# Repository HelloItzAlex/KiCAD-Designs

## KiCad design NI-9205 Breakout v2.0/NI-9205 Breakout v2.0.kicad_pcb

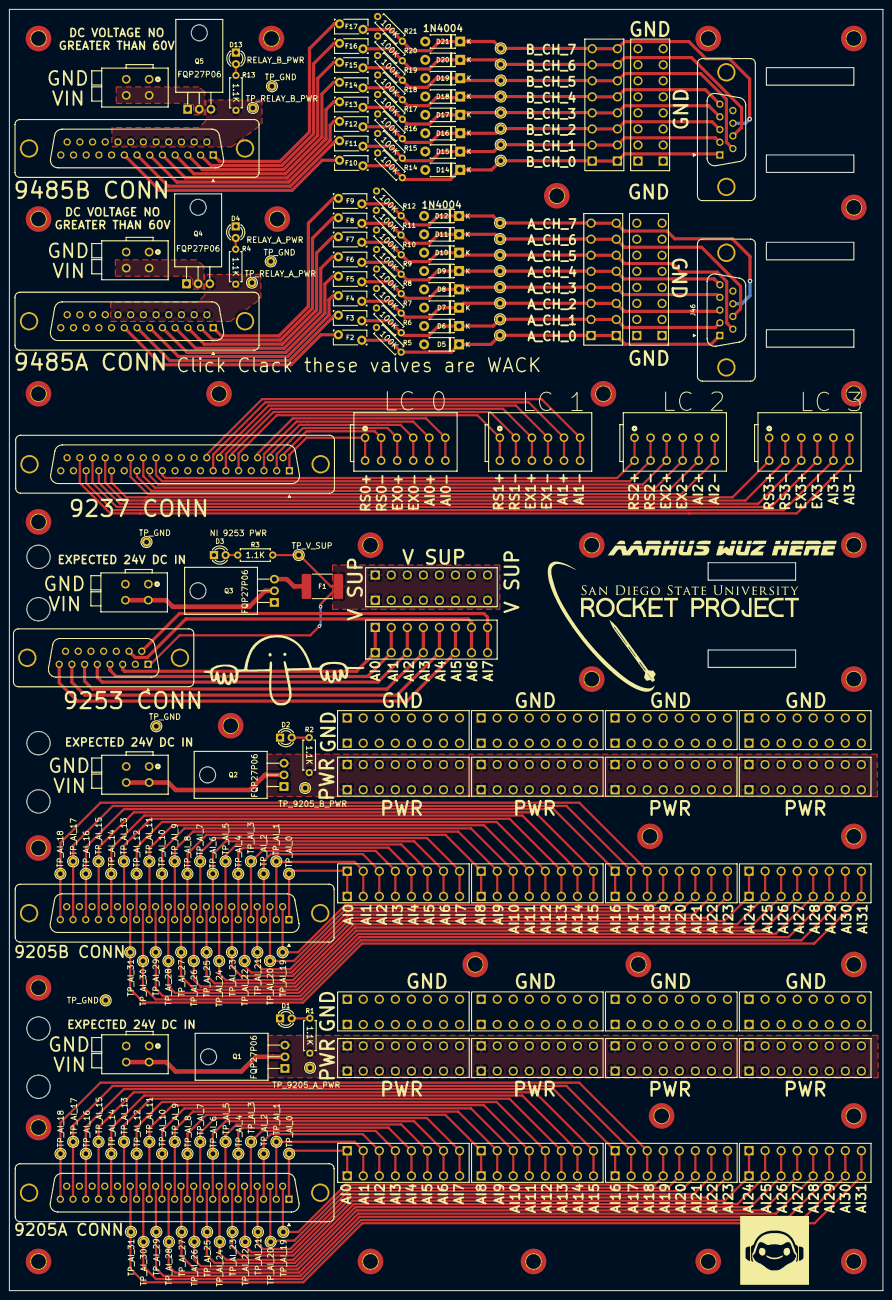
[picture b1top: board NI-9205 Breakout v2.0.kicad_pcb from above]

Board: 2 copper layers, 190.5 x 279.4 mm, 235 parts (0 on the bottom side), 145 nets.

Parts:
D1, D2, D3, D4, D13: LED; LED_D3.0mm
D5, D6, D7, D8, D9, D10, D11, D12, D14, D15, D16, D17, D18, D19, D20, D21: 1N4004; D_DO-41_SOD81_P7.62mm_Horizontal
F1: 0ZCF0100AF2A; Fuse_2920_7451Metric_Pad2.10x5.45mm_HandSolder
F2, F3, F4, F5, F6, F7, F8, F9, F10, F11, F12, F13, F14, F15, F16, F17: 0ZRP0065FF1E; Fuse_Bourns_MF-RG300
H1, H2, H3, H4, H5, H6, H7, H8, H9, H10, H11, H12, H13, H14, H15, H16, H17, H18, H19, H20, H21, H22, H23, H24, H25, H26, H27, H28, H29, H30, H31, H32, H33, H34: MountingHole_Pad; MountingHole_3.2mm_M3_DIN965_Pad_TopBottom
J1, J15: NI9205CONN; DSUB-37_Pins_Vertical_P2.77x2.84mm_MountingHoles
J2, J16, J32, J39, J43: PWRCONN; CONN2_2601-1102_WAG
J3, J6, J9, J13, J17, J20, J23, J27: 24VCONN; RHDR16W80P550X350_2X8_2870X850X1420P
J4, J7, J10, J14, J18, J21, J24, J28, J41, J45: GNDCONN; RHDR16W80P550X350_2X8_2870X850X1420P
J5, J8, J11, J12, J19, J22, J25, J26, J30, J40, J44: AICONN; RHDR16W80P550X350_2X8_2870X850X1420P
J29: NI9253CONN; DSUB-15_Pins_Vertical_P2.77x2.84mm_MountingHoles
J31: VSUPCONN; RHDR16W80P550X350_2X8_2870X850X1420P
J33: NI9237CONN; DSUB-37_Pins_Vertical_P2.77x2.84mm_MountingHoles
J34: LC0; CONN6_2601-3106_WAG
J35: LC1; CONN6_2601-3106_WAG
J36: LC2; CONN6_2601-3106_WAG
J37: LC3; CONN6_2601-3106_WAG
J38, J42: NI9485CONN; DSUB-25_Pins_Vertical_P2.77x2.84mm_MountingHoles
J46: NI_9485A_D-SUB; DSUB-9_Pins_Vertical_P2.77x2.84mm_MountingHoles
J47: NI_9485B_D-SUB; DSUB-9_Pins_Vertical_P2.77x2.84mm_MountingHoles
Q1, Q2, Q3, Q4, Q5: FQP27P06; TO-220-3_Horizontal_TabDown
R1, R2, R3, R4, R13: 1.1k; R_Axial_DIN0207_L6.3mm_D2.5mm_P7.62mm_Horizontal
R5, R6, R7, R8, R9, R10, R11, R12, R14, R15, R16, R17, R18, R19, R20, R21: 100K; R_Axial_DIN0207_L6.3mm_D2.5mm_P7.62mm_Horizontal
TP1, TP2, TP3, TP4, TP5, TP6, TP7, TP8, TP9, TP10, TP11, TP12, TP13, TP14, TP15, TP16, TP17, TP18, TP19, TP20, TP21, TP22, TP23, TP24, TP25, TP26, TP27, TP28, TP29, TP30, TP31, TP32, TP33, TP34, TP35, TP36, TP37, TP38, TP39, TP40, TP41, TP42, TP43, TP44, TP45, TP46, TP47, TP48, TP49, TP50, TP51, TP52, TP53, TP54, TP55, TP56, TP57, TP58, TP59, TP60, TP61, TP62, TP63, TP64, TP65, TP66, TP67, TP68, TP69, TP70, TP71, TP72, TP73, TP74, TP75, TP76, TP77, TP78, TP79, TP80, TP81, TP82, TP83, TP84, TP85, TP86, TP87, TP88, TP89, TP90: TestPoint; TestPoint_THTPad_D2.0mm_Drill1.0mm

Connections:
/V_IN_A: J39.3 (2_1), J39.4 (2_2), Q4.2 (D)
/V_IN_B: J43.3 (2_1), J43.4 (2_2), Q5.2 (D)
AI0: J29.3, J30.1, J30.2
AI1: J29.4, J30.3, J30.4
AI2: J29.5, J30.5, J30.6
AI3: J29.6, J30.7, J30.8
AI4: J29.7, J30.9, J30.10
AI5: J29.8, J30.11, J30.12
AI6: J29.10, J30.13, J30.14
AI7: J29.9, J30.15, J30.16
COM: D1.1 (K), D2.1 (K), D3.1 (K), D4.1 (K), D5.2 (A), D6.2 (A), D7.2 (A), D8.2 (A), D9.2 (A), D10.2 (A), D11.2 (A), D12.2 (A), D13.1 (K), D14.2 (A), D15.2 (A), D16.2 (A), D17.2 (A), D18.2 (A), D19.2 (A), D20.2 (A), D21.2 (A), J1.0 (PAD), J1.33, J2.1 (1_1), J2.2 (1_2), J4.1, J4.2, J4.3, J4.4, J4.5, J4.6, J4.7, J4.8, J4.9, J4.10, J4.11, J4.12, J4.13, J4.14, J4.15, J4.16, J7.1, J7.2, J7.3, J7.4, J7.5, J7.6, J7.7, J7.8, J7.9, J7.10, J7.11, J7.12, J7.13, J7.14, J7.15, J7.16, J10.1, J10.2, J10.3, J10.4, J10.5, J10.6, J10.7, J10.8, J10.9, J10.10, J10.11, J10.12, J10.13, J10.14, J10.15, J10.16, J14.1, J14.2, J14.3, J14.4, J14.5, J14.6, J14.7, J14.8, J14.9, J14.10, J14.11, J14.12, J14.13, J14.14, J14.15, J14.16, J15.0 (PAD), J15.33, J16.1 (1_1), J16.2 (1_2), J18.1, J18.2, J18.3, J18.4, J18.5, J18.6, J18.7, J18.8, J18.9, J18.10, J18.11, J18.12, J18.13, J18.14, J18.15, J18.16, J21.1, J21.2, J21.3, J21.4, J21.5, J21.6, J21.7, J21.8, J21.9, J21.10, J21.11, J21.12, J21.13, J21.14, J21.15, J21.16, J24.1, J24.2, J24.3, J24.4, J24.5, J24.6, J24.7, J24.8, J24.9, J24.10, J24.11, J24.12, J24.13, J24.14, J24.15, J24.16, J28.1, J28.2, J28.3, J28.4, J28.5, J28.6, J28.7, J28.8, J28.9, J28.10, J28.11, J28.12, J28.13, J28.14, J28.15, J28.16, J29.0 (PAD), J29.2, J32.1 (1_1), J32.2 (1_2), J38.0 (PAD), J39.1 (1_1), J39.2 (1_2), J41.1, J41.2, J41.3, J41.4, J41.5, J41.6, J41.7, J41.8, J41.9, J41.10, J41.11, J41.12, J41.13, J41.14, J41.15, J41.16, J42.0 (PAD), J43.1 (1_1), J43.2 (1_2), J45.1, J45.2, J45.3, J45.4, J45.5, J45.6, J45.7, J45.8, J45.9, J45.10, J45.11, J45.12, J45.13, J45.14, J45.15, J45.16, J46.0 (PAD), J46.9, J47.0 (PAD)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
EX0+: J33.2, J34.5 (3_1), J34.6 (3_2)
EX0-: J33.21, J34.7 (4_1), J34.8 (4_2)
EX1+: J33.6, J35.5 (3_1), J35.6 (3_2)
EX1-: J33.25, J35.7 (4_1), J35.8 (4_2)
EX2+: J33.12, J36.5 (3_1), J36.6 (3_2)
EX2-: J33.31, J36.7 (4_1), J36.8 (4_2)
EX3+: J33.16, J37.5 (3_1), J37.6 (3_2)
EX3-: J33.35, J37.7 (4_1), J37.8 (4_2)
NI9205A_AI0: J1.1, J5.1, J5.2, TP3.1
NI9205A_AI1: J1.2, J5.3, J5.4, TP4.1
NI9205A_AI2: J1.3, J5.5, J5.6, TP5.1
NI9205A_AI3: J1.4, J5.7, J5.8, TP6.1
NI9205A_AI4: J1.5, J5.9, J5.10, TP7.1
NI9205A_AI5: J1.6, J5.11, J5.12, TP8.1
NI9205A_AI6: J1.7, J5.13, J5.14, TP9.1
NI9205A_AI7: J1.8, J5.15, J5.16, TP10.1
NI9205A_AI8: J1.9, J8.1, J8.2, TP11.1
NI9205A_AI9: J1.10, J8.3, J8.4, TP12.1
NI9205A_AI10: J1.11, J8.5, J8.6, TP13.1
NI9205A_AI11: J1.12, J8.7, J8.8, TP14.1
NI9205A_AI12: J1.13, J8.9, J8.10, TP15.1
NI9205A_AI13: J1.14, J8.11, J8.12, TP16.1
NI9205A_AI14: J1.15, J8.13, J8.14, TP17.1
NI9205A_AI15: J1.16, J8.15, J8.16, TP18.1
NI9205A_AI16: J1.17, J11.1, J11.2, TP19.1
NI9205A_AI17: J1.18, J11.3, J11.4, TP20.1
NI9205A_AI18: J1.19, J11.5, J11.6, TP21.1
NI9205A_AI19: J1.20, J11.7, J11.8, TP22.1
NI9205A_AI20: J1.21, J11.9, J11.10, TP23.1
NI9205A_AI21: J1.22, J11.11, J11.12, TP24.1
NI9205A_AI22: J1.23, J11.13, J11.14, TP25.1
NI9205A_AI23: J1.24, J11.15, J11.16, TP26.1
NI9205A_AI24: J1.25, J12.1, J12.2, TP27.1
NI9205A_AI25: J1.26, J12.3, J12.4, TP28.1
NI9205A_AI26: J1.27, J12.5, J12.6, TP29.1
NI9205A_AI27: J1.28, J12.7, J12.8, TP30.1
NI9205A_AI28: J1.29, J12.9, J12.10, TP31.1
NI9205A_AI29: J1.30, J12.11, J12.12, TP32.1
NI9205A_AI30: J1.31, J12.13, J12.14, TP33.1
NI9205A_AI31: J1.32, J12.15, J12.16, TP34.1
NI9205A_PWR: J3.1, J3.2, J3.3, J3.4, J3.5, J3.6, J3.7, J3.8, J3.9, J3.10, J3.11, J3.12, J3.13, J3.14, J3.15, J3.16, J6.1, J6.2, J6.3, J6.4, J6.5, J6.6, J6.7, J6.8, J6.9, J6.10, J6.11, J6.12, J6.13, J6.14, J6.15, J6.16, J9.1, J9.2, J9.3, J9.4, J9.5, J9.6, J9.7, J9.8, J9.9, J9.10, J9.11, J9.12, J9.13, J9.14, J9.15, J9.16, J13.1, J13.2, J13.3, J13.4, J13.5, J13.6, J13.7, J13.8, J13.9, J13.10, J13.11, J13.12, J13.13, J13.14, J13.15, J13.16, Q1.3 (S), R1.1, TP1.1
NI9205B_AI0: J15.1, J19.1, J19.2, TP35.1
NI9205B_AI1: J15.2, J19.3, J19.4, TP36.1
NI9205B_AI2: J15.3, J19.5, J19.6, TP37.1
NI9205B_AI3: J15.4, J19.7, J19.8, TP38.1
NI9205B_AI4: J15.5, J19.9, J19.10, TP39.1
NI9205B_AI5: J15.6, J19.11, J19.12, TP40.1
NI9205B_AI6: J15.7, J19.13, J19.14, TP41.1
NI9205B_AI7: J15.8, J19.15, J19.16, TP42.1
NI9205B_AI8: J15.9, J22.1, J22.2, TP43.1
NI9205B_AI9: J15.10, J22.3, J22.4, TP44.1
NI9205B_AI10: J15.11, J22.5, J22.6, TP45.1
NI9205B_AI11: J15.12, J22.7, J22.8, TP46.1
NI9205B_AI12: J15.13, J22.9, J22.10, TP47.1
NI9205B_AI13: J15.14, J22.11, J22.12, TP48.1
NI9205B_AI14: J15.15, J22.13, J22.14, TP49.1
NI9205B_AI15: J15.16, J22.15, J22.16, TP50.1
NI9205B_AI16: J15.17, J25.1, J25.2, TP51.1
NI9205B_AI17: J15.18, J25.3, J25.4, TP52.1
NI9205B_AI18: J15.19, J25.5, J25.6, TP53.1
NI9205B_AI19: J15.20, J25.7, J25.8, TP54.1
NI9205B_AI20: J15.21, J25.9, J25.10, TP55.1
NI9205B_AI21: J15.22, J25.11, J25.12, TP56.1
NI9205B_AI22: J15.23, J25.13, J25.14, TP57.1
NI9205B_AI23: J15.24, J25.15, J25.16, TP58.1
NI9205B_AI24: J15.25, J26.1, J26.2, TP59.1
NI9205B_AI25: J15.26, J26.3, J26.4, TP60.1
NI9205B_AI26: J15.27, J26.5, J26.6, TP61.1
NI9205B_AI27: J15.28, J26.7, J26.8, TP62.1
NI9205B_AI28: J15.29, J26.9, J26.10, TP63.1
NI9205B_AI29: J15.30, J26.11, J26.12, TP64.1
NI9205B_AI30: J15.31, J26.13, J26.14, TP65.1
NI9205B_AI31: J15.32, J26.15, J26.16, TP66.1
NI9205B_PWR: J17.1, J17.2, J17.3, J17.4, J17.5, J17.6, J17.7, J17.8, J17.9, J17.10, J17.11, J17.12, J17.13, J17.14, J17.15, J17.16, J20.1, J20.2, J20.3, J20.4, J20.5, J20.6, J20.7, J20.8, J20.9, J20.10, J20.11, J20.12, J20.13, J20.14, J20.15, J20.16, J23.1, J23.2, J23.3, J23.4, J23.5, J23.6, J23.7, J23.8, J23.9, J23.10, J23.11, J23.12, J23.13, J23.14, J23.15, J23.16, J27.1, J27.2, J27.3, J27.4, J27.5, J27.6, J27.7, J27.8, J27.9, J27.10, J27.11, J27.12, J27.13, J27.14, J27.15, J27.16, Q2.3 (S), R2.1, TP89.1
NI9237_AI0+: J33.3, J34.9 (5_1), J34.10 (5_2)
NI9237_AI0-: J33.22, J34.11 (6_1), J34.12 (6_2)
NI9237_AI1+: J33.7, J35.9 (5_1), J35.10 (5_2)
NI9237_AI1-: J33.26, J35.11 (6_1), J35.12 (6_2)
NI9237_AI2+: J33.13, J36.9 (5_1), J36.10 (5_2)
NI9237_AI2-: J33.32, J36.11 (6_1), J36.12 (6_2)
NI9237_AI3+: J33.17, J37.9 (5_1), J37.10 (5_2)
NI9237_AI3-: J33.36, J37.11 (6_1), J37.12 (6_2)
NI9485A_24V+: J38.14, J38.15, J38.16, J38.17, J38.18, J38.19, J38.20, J38.21, Q4.3 (S), R4.1, TP69.1
NI9485A_CH0B: D5.1 (K), F2.2, J40.1, J40.2, J46.1, R5.1, TP71.1
NI9485A_CH1B: D6.1 (K), F3.2, J40.3, J40.4, J46.2, R6.1, TP72.1
NI9485A_CH2B: D7.1 (K), F4.2, J40.5, J40.6, J46.3, R7.1, TP73.1
NI9485A_CH3B: D8.1 (K), F5.2, J40.7, J40.8, J46.4, R8.1, TP74.1
NI9485A_CH4B: D9.1 (K), F6.2, J40.9, J40.10, J46.5, R9.1, TP75.1
NI9485A_CH5B: D10.1 (K), F7.2, J40.11, J40.12, J46.6, R10.1, TP76.1
NI9485A_CH6B: D11.1 (K), F8.2, J40.13, J40.14, J46.7, R11.1, TP77.1
NI9485A_CH7B: D12.1 (K), F9.2, J40.15, J40.16, J46.8, R12.1, TP78.1
NI9485B_24V+: J42.14, J42.15, J42.16, J42.17, J42.18, J42.19, J42.20, J42.21, Q5.3 (S), R13.1, TP79.1
NI9485B_CH0B: D14.1 (K), F10.2, J44.1, J44.2, J47.1, R14.1, TP81.1
NI9485B_CH1B: D15.1 (K), F11.2, J44.3, J44.4, J47.2, R15.1, TP82.1
NI9485B_CH2B: D16.1 (K), F12.2, J44.5, J44.6, J47.3, R16.1, TP83.1
NI9485B_CH3B: D17.1 (K), F13.2, J44.7, J44.8, J47.4, R17.1, TP84.1
NI9485B_CH4B: D18.1 (K), F14.2, J44.9, J44.10, J47.5, R18.1, TP85.1
NI9485B_CH5B: D19.1 (K), F15.2, J44.11, J44.12, J47.6, R19.1, TP86.1
NI9485B_CH6B: D20.1 (K), F16.2, J44.13, J44.14, J47.7, R20.1, TP87.1
NI9485B_CH7B: D21.1 (K), F17.2, J44.15, J44.16, J47.8, R21.1, TP88.1
unnamed: D1.2 (A), R1.2
unnamed: D2.2 (A), R2.2
unnamed: D3.2 (A), R3.2
unnamed: D4.2 (A), R4.2
unnamed: D13.2 (A), R13.2
unnamed: F2.1, J38.8
unnamed: F3.1, J38.7
unnamed: F4.1, J38.6
unnamed: F5.1, J38.5
unnamed: F6.1, J38.4
unnamed: F7.1, J38.3
unnamed: F8.1, J38.2
unnamed: F9.1, J38.1
unnamed: F10.1, J42.8
unnamed: F11.1, J42.7
unnamed: F12.1, J42.6
unnamed: F13.1, J42.5
unnamed: F14.1, J42.4
unnamed: F15.1, J42.3
unnamed: F16.1, J42.2
unnamed: F17.1, J42.1
unnamed: J2.3 (2_1), J2.4 (2_2), Q1.2 (D)
unnamed: J16.3 (2_1), J16.4 (2_2), Q2.2 (D)
unnamed: J32.3 (2_1), J32.4 (2_2), Q3.2 (D)
unnamed: F1.1, Q3.3 (S)
RS0+: J33.1, J34.1 (1_1), J34.2 (1_2)
RS0-: J33.20, J34.3 (2_1), J34.4 (2_2)
RS1+: J33.5, J35.1 (1_1), J35.2 (1_2)
RS1-: J33.24, J35.3 (2_1), J35.4 (2_2)
RS2+: J33.11, J36.1 (1_1), J36.2 (1_2)
RS2-: J33.30, J36.3 (2_1), J36.4 (2_2)
RS3+: J33.15, J37.1 (1_1), J37.2 (1_2)
RS3-: J33.34, J37.3 (2_1), J37.4 (2_2)
VSUP: F1.2, J29.1, J31.1, J31.2, J31.3, J31.4, J31.5, J31.6, J31.7, J31.8, J31.9, J31.10, J31.11, J31.12, J31.13, J31.14, J31.15, J31.16, R3.1, TP67.1

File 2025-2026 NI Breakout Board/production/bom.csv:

Designator,Footprint,Quantity,Value,LCSC Part #
"D1, D13, D2, D3, D4",LED_D3.0mm,5,LED,
"D10, D11, D12, D14, D15, D16, D17, D18, D19, D20, D21, D5, D6, D7, D8, D9",D_DO-41_SOD81_P7.62mm_Horizontal,16,1N4004,
F1,2920,1,0ZCF0100AF2A,
"F10, F11, F12, F13, F14, F15, F16, F17, F2, F3, F4, F5, F6, F7, F8, F9",Fuse_Bourns_MF-RG300,16,0ZRP0065FF1E,
"J1, J15",DSUB-37_Pins_Vertical_P2.77x2.84mm_MountingHoles,2,NI9205CONN,
"J10, J14, J18, J21, J24, J28, J4, J41, J45, J7",RHDR16W80P550X350_2X8_2870X850X1420P,10,GNDCONN,
"J11, J12, J19, J22, J25, J26, J30, J40, J44, J5, J8",RHDR16W80P550X350_2X8_2870X850X1420P,11,AICONN,
"J13, J17, J20, J23, J27, J3, J6, J9",RHDR16W80P550X350_2X8_2870X850X1420P,8,24VCONN,
"J16, J2, J32, J39, J43",CONN2_2601-1102_WAG,5,PWRCONN,
J29,DSUB-15_Pins_Vertical_P2.77x2.84mm_MountingHoles,1,NI9253CONN,
J31,RHDR16W80P550X350_2X8_2870X850X1420P,1,VSUPCONN,
J33,DSUB-37_Pins_Vertical_P2.77x2.84mm_MountingHoles,1,NI9237CONN,
J34,CONN6_2601-3106_WAG,1,LC0,
J35,CONN6_2601-3106_WAG,1,LC1,
J36,CONN6_2601-3106_WAG,1,LC2,
J37,CONN6_2601-3106_WAG,1,LC3,
"J38, J42",DSUB-25_Pins_Vertical_P2.77x2.84mm_MountingHoles,2,NI9485CONN,
J46,DSUB-9_Pins_Vertical_P2.77x2.84mm_MountingHoles,1,NI_9485A_D-SUB,
J47,DSUB-9_Pins_Vertical_P2.77x2.84mm_MountingHoles,1,NI_9485B_D-SUB,
"Q1, Q2, Q3, Q4, Q5",TO-220-3_Horizontal_TabDown,5,FQP27P06,
"R1, R13, R2, R3, R4",R_Axial_DIN0207_L6.3mm_D2.5mm_P7.62mm_Horizontal,5,1.1k,
"R10, R11, R12, R14, R15, R16, R17, R18, R19, R20, R21, R5, R6, R7, R8, R9",R_Axial_DIN0207_L6.3mm_D2.5mm_P7.62mm_Horizontal,16,100K,
"TP1, TP10, TP11, TP12, TP13, TP14, TP15, TP16, TP17, TP18, TP19, TP2, TP20, TP21, TP22, TP23, TP24, TP25, TP26, TP27, TP28, TP29, TP3, TP30, TP31, TP32, TP33, TP34, TP35, TP36, TP37, TP38, TP39, TP4, TP40, TP41, TP42, TP43, TP44, TP45, TP46, TP47, TP48, TP49, TP5, TP50, TP51, TP52, TP53, TP54, TP55, TP56, TP57, TP58, TP59, TP6, TP60, TP61, TP62, TP63, TP64, TP65, TP66, TP67, TP68, TP69, TP7, TP70, TP71, TP72, TP73, TP74, TP75, TP76, TP77, TP78, TP79, TP8, TP80, TP81, TP82, TP83, TP84, TP85, TP86, TP87, TP88, TP89, TP9, TP90",TestPoint_THTPad_D2.0mm_Drill1.0mm,90,TestPoint,

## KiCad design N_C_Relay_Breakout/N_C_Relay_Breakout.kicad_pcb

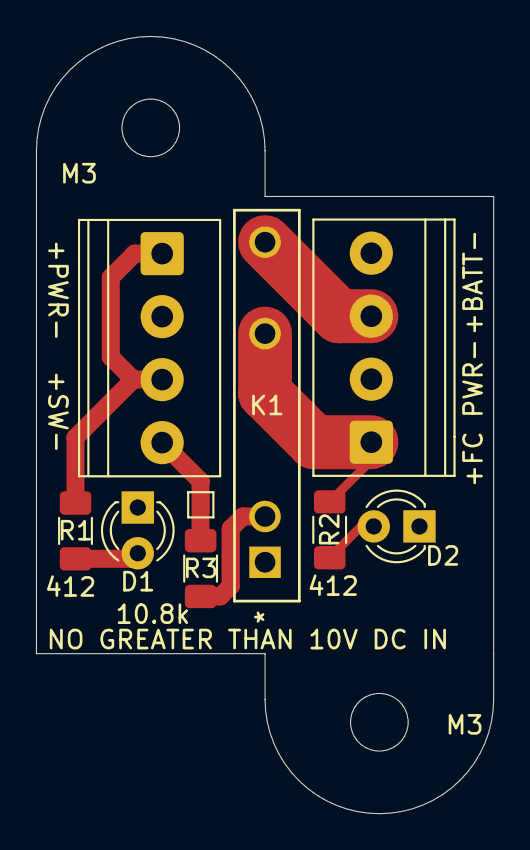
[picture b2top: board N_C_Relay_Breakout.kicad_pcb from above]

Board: 2 copper layers, 25.4 x 43.2 mm, 11 parts (0 on the bottom side), 8 nets.

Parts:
D1, D2: LED; LED_D3.0mm
H1, H2: MountingHole; MountingHole_3.2mm_M3
J1: PWR_IN; TerminalBlock_Phoenix_PT-1,5-4-3.5-H_1x04_P3.50mm_Horizontal
J2: PWR_OUT; TerminalBlock_Phoenix_PT-1,5-4-3.5-H_1x04_P3.50mm_Horizontal
K1: CPC1705Y; CPC1705Y_IXY
R1, R2, R3: R; R_1206_3216Metric_Pad1.30x1.75mm_HandSolder
TP1: SW_IN_TP; TestPoint_Pad_1.0x1.0mm

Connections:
FC_PWR_IN: J2.3, K1.4
FC_PWR_OUT: J2.1, K1.3, R2.1
GND: D1.1 (K), D2.1 (K), J1.2, J2.2, J2.4, K1.1
unnamed: D1.2 (A), R1.2
unnamed: D2.2 (A), R2.2
unnamed: K1.2, R3.2
PWR_IN: J1.1, J1.3, R1.1
SW_IN: J1.4, R3.1, TP1.1

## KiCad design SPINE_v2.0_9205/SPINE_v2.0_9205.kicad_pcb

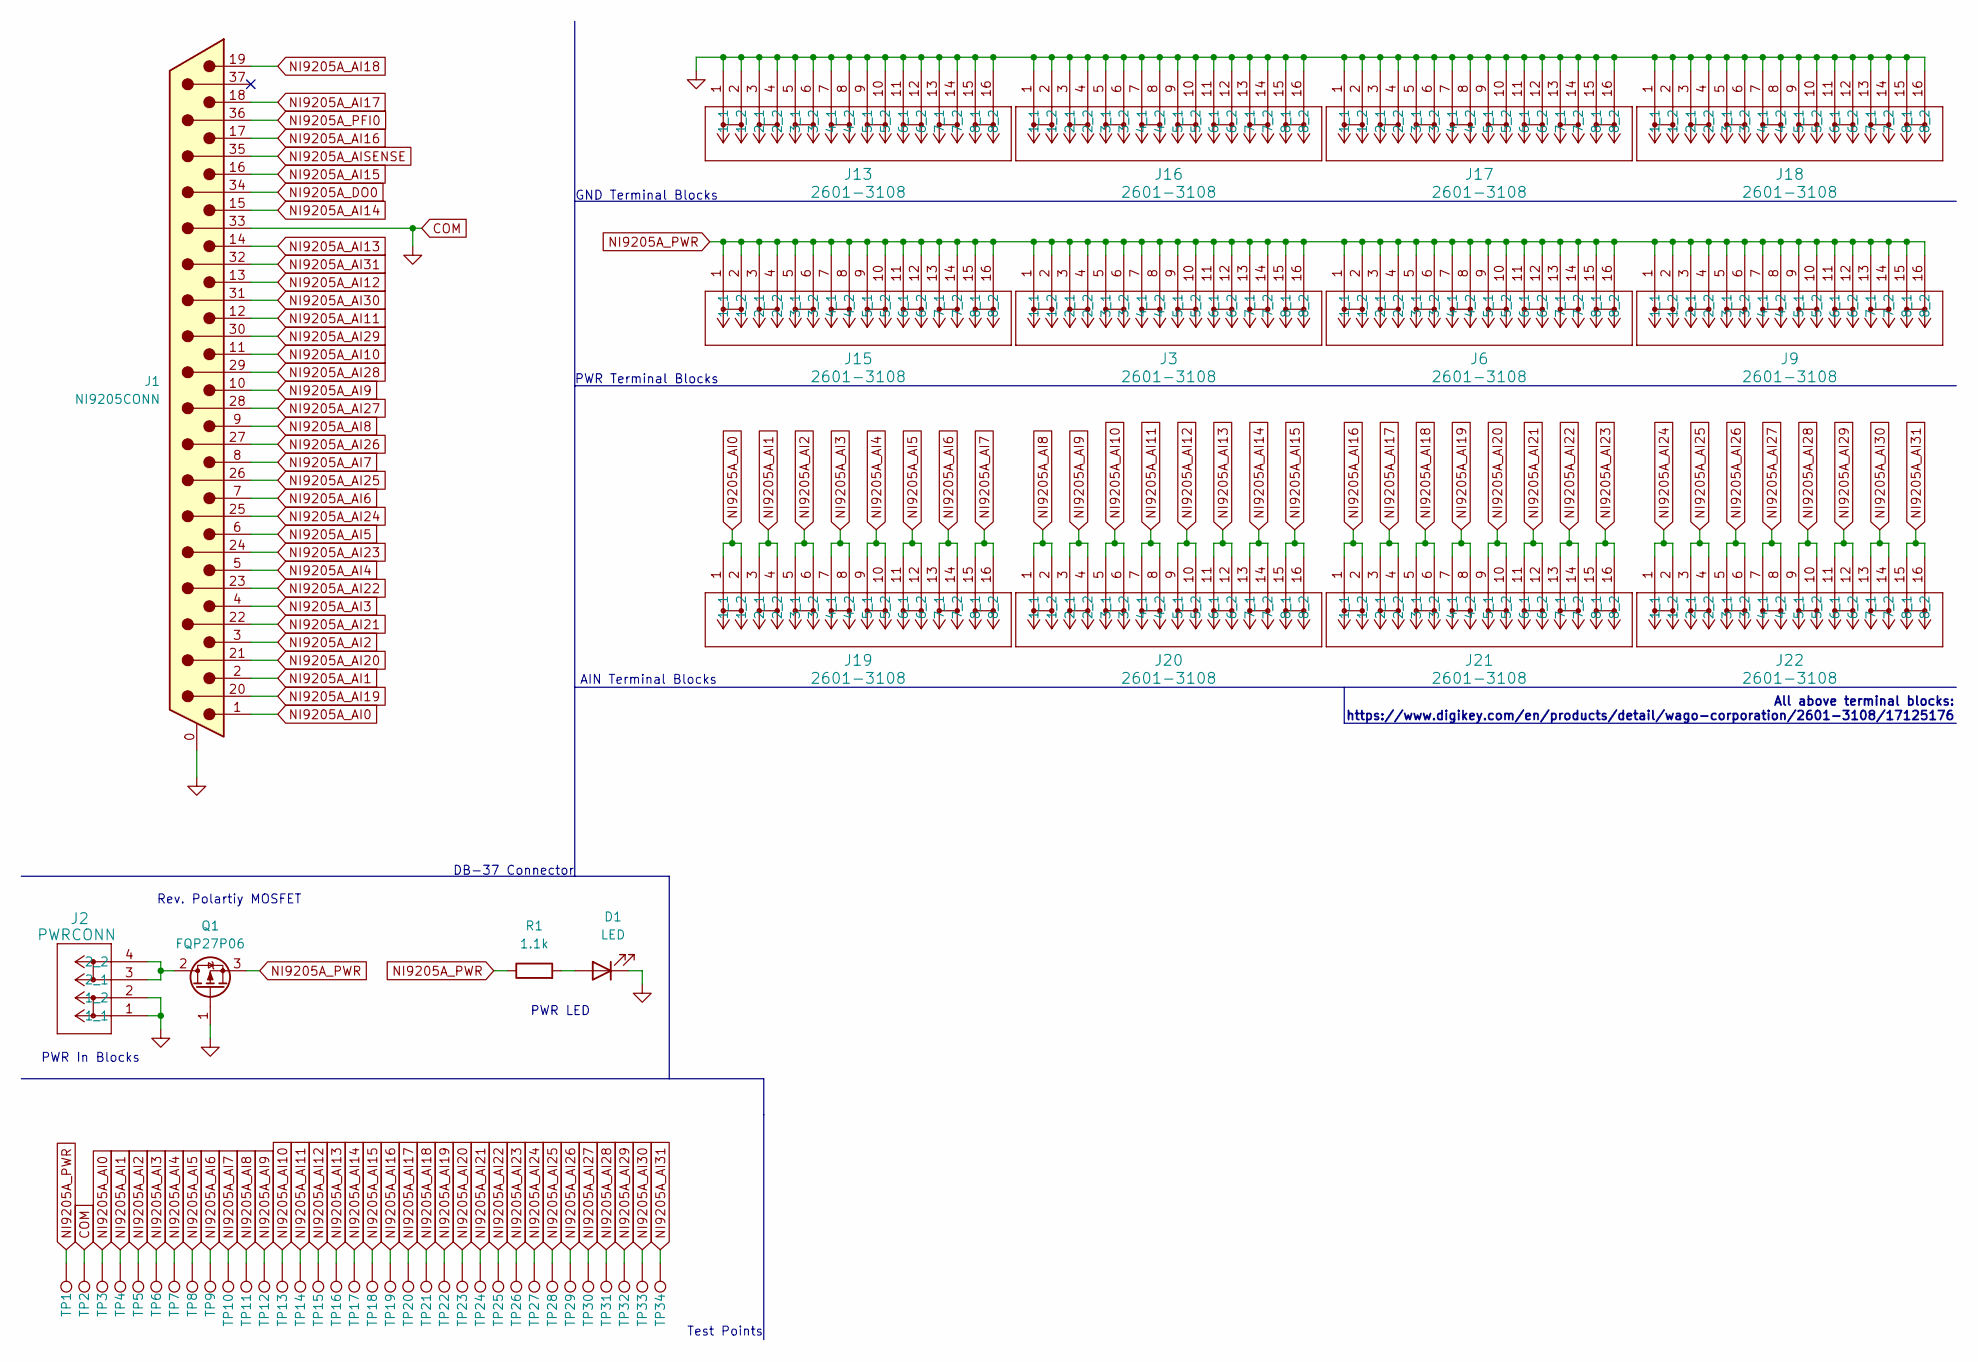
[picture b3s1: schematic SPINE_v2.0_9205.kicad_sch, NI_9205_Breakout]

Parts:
D1: LED; LED_D3.0mm
J1: NI9205CONN; DSUB-37_Pins_Vertical_P2.77x2.84mm_MountingHoles
J2: PWRCONN; CONN2_2601-1102_WAG
J3, J6, J9, J13, J15, J16, J17, J18, J19, J20, J21, J22: 2601-3108; CONN8_2601-3108_WAG
Q1: FQP27P06; TO-220-3_Horizontal_TabDown
R1: 1.1k; R_Axial_DIN0207_L6.3mm_D2.5mm_P7.62mm_Horizontal
TP1, TP2, TP3, TP4, TP5, TP6, TP7, TP8, TP9, TP10, TP11, TP12, TP13, TP14, TP15, TP16, TP17, TP18, TP19, TP20, TP21, TP22, TP23, TP24, TP25, TP26, TP27, TP28, TP29, TP30, TP31, TP32, TP33, TP34: TestPoint; TestPoint_THTPad_D2.0mm_Drill1.0mm

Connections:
COM: D1.1 (K), J1.0 (PAD), J1.33, J2.1 (1_1), J2.2 (1_2), J13.1 (1_1), J13.2 (1_2), J13.3 (2_1), J13.4 (2_2), J13.5 (3_1), J13.6 (3_2), J13.7 (4_1), J13.8 (4_2), J13.9 (5_1), J13.10 (5_2), J13.11 (6_1), J13.12 (6_2), J13.13 (7_1), J13.14 (7_2), J13.15 (8_1), J13.16 (8_2), J16.1 (1_1), J16.2 (1_2), J16.3 (2_1), J16.4 (2_2), J16.5 (3_1), J16.6 (3_2), J16.7 (4_1), J16.8 (4_2), J16.9 (5_1), J16.10 (5_2), J16.11 (6_1), J16.12 (6_2), J16.13 (7_1), J16.14 (7_2), J16.15 (8_1), J16.16 (8_2), J17.1 (1_1), J17.2 (1_2), J17.3 (2_1), J17.4 (2_2), J17.5 (3_1), J17.6 (3_2), J17.7 (4_1), J17.8 (4_2), J17.9 (5_1), J17.10 (5_2), J17.11 (6_1), J17.12 (6_2), J17.13 (7_1), J17.14 (7_2), J17.15 (8_1), J17.16 (8_2), J18.1 (1_1), J18.2 (1_2), J18.3 (2_1), J18.4 (2_2), J18.5 (3_1), J18.6 (3_2), J18.7 (4_1), J18.8 (4_2), J18.9 (5_1), J18.10 (5_2), J18.11 (6_1), J18.12 (6_2), J18.13 (7_1), J18.14 (7_2), J18.15 (8_1), J18.16 (8_2), Q1.1 (G), TP2.1
NI9205A_AI0: J1.1, J19.1 (1_1), J19.2 (1_2), TP3.1
NI9205A_AI1: J1.2, J19.3 (2_1), J19.4 (2_2), TP4.1
NI9205A_AI2: J1.3, J19.5 (3_1), J19.6 (3_2), TP5.1
NI9205A_AI3: J1.4, J19.7 (4_1), J19.8 (4_2), TP6.1
NI9205A_AI4: J1.5, J19.9 (5_1), J19.10 (5_2), TP7.1
NI9205A_AI5: J1.6, J19.11 (6_1), J19.12 (6_2), TP8.1
NI9205A_AI6: J1.7, J19.13 (7_1), J19.14 (7_2), TP9.1
NI9205A_AI7: J1.8, J19.15 (8_1), J19.16 (8_2), TP10.1
NI9205A_AI8: J1.9, J20.1 (1_1), J20.2 (1_2), TP11.1
NI9205A_AI9: J1.10, J20.3 (2_1), J20.4 (2_2), TP12.1
NI9205A_AI10: J1.11, J20.5 (3_1), J20.6 (3_2), TP13.1
NI9205A_AI11: J1.12, J20.7 (4_1), J20.8 (4_2), TP14.1
NI9205A_AI12: J1.13, J20.9 (5_1), J20.10 (5_2), TP15.1
NI9205A_AI13: J1.14, J20.11 (6_1), J20.12 (6_2), TP16.1
NI9205A_AI14: J1.15, J20.13 (7_1), J20.14 (7_2), TP17.1
NI9205A_AI15: J1.16, J20.15 (8_1), J20.16 (8_2), TP18.1
NI9205A_AI16: J1.17, J21.1 (1_1), J21.2 (1_2), TP19.1
NI9205A_AI17: J1.18, J21.3 (2_1), J21.4 (2_2), TP20.1
NI9205A_AI18: J1.19, J21.5 (3_1), J21.6 (3_2), TP21.1
NI9205A_AI19: J1.20, J21.7 (4_1), J21.8 (4_2), TP22.1
NI9205A_AI20: J1.21, J21.9 (5_1), J21.10 (5_2), TP23.1
NI9205A_AI21: J1.22, J21.11 (6_1), J21.12 (6_2), TP24.1
NI9205A_AI22: J1.23, J21.13 (7_1), J21.14 (7_2), TP25.1
NI9205A_AI23: J1.24, J21.15 (8_1), J21.16 (8_2), TP26.1
NI9205A_AI24: J1.25, J22.1 (1_1), J22.2 (1_2), TP27.1
NI9205A_AI25: J1.26, J22.3 (2_1), J22.4 (2_2), TP28.1
NI9205A_AI26: J1.27, J22.5 (3_1), J22.6 (3_2), TP29.1
NI9205A_AI27: J1.28, J22.7 (4_1), J22.8 (4_2), TP30.1
NI9205A_AI28: J1.29, J22.9 (5_1), J22.10 (5_2), TP31.1
NI9205A_AI29: J1.30, J22.11 (6_1), J22.12 (6_2), TP32.1
NI9205A_AI30: J1.31, J22.13 (7_1), J22.14 (7_2), TP33.1
NI9205A_AI31: J1.32, J22.15 (8_1), J22.16 (8_2), TP34.1
NI9205A_AISENSE: J1.35
NI9205A_DO0: J1.34
NI9205A_PFI0: J1.36
NI9205A_PWR: J3.1 (1_1), J3.2 (1_2), J3.3 (2_1), J3.4 (2_2), J3.5 (3_1), J3.6 (3_2), J3.7 (4_1), J3.8 (4_2), J3.9 (5_1), J3.10 (5_2), J3.11 (6_1), J3.12 (6_2), J3.13 (7_1), J3.14 (7_2), J3.15 (8_1), J3.16 (8_2), J6.1 (1_1), J6.2 (1_2), J6.3 (2_1), J6.4 (2_2), J6.5 (3_1), J6.6 (3_2), J6.7 (4_1), J6.8 (4_2), J6.9 (5_1), J6.10 (5_2), J6.11 (6_1), J6.12 (6_2), J6.13 (7_1), J6.14 (7_2), J6.15 (8_1), J6.16 (8_2), J9.1 (1_1), J9.2 (1_2), J9.3 (2_1), J9.4 (2_2), J9.5 (3_1), J9.6 (3_2), J9.7 (4_1), J9.8 (4_2), J9.9 (5_1), J9.10 (5_2), J9.11 (6_1), J9.12 (6_2), J9.13 (7_1), J9.14 (7_2), J9.15 (8_1), J9.16 (8_2), J15.1 (1_1), J15.2 (1_2), J15.3 (2_1), J15.4 (2_2), J15.5 (3_1), J15.6 (3_2), J15.7 (4_1), J15.8 (4_2), J15.9 (5_1), J15.10 (5_2), J15.11 (6_1), J15.12 (6_2), J15.13 (7_1), J15.14 (7_2), J15.15 (8_1), J15.16 (8_2), Q1.3 (S), R1.1, TP1.1
unnamed: D1.2 (A), R1.2
unnamed: J2.3 (2_1), J2.4 (2_2), Q1.2 (D)

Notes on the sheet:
PWR In Blocks
All above terminal blocks: https://www.digikey.com/en/products/detail/wago-corporation/2601-3108/17125176
GND Terminal Blocks
PWR LED
AIN Terminal Blocks
DB-37 Connector
Rev. Polartiy MOSFET
Test Points
PWR Terminal Blocks

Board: 2 copper layers, 51 parts (0 on the bottom side), 36 nets, no tracks yet.

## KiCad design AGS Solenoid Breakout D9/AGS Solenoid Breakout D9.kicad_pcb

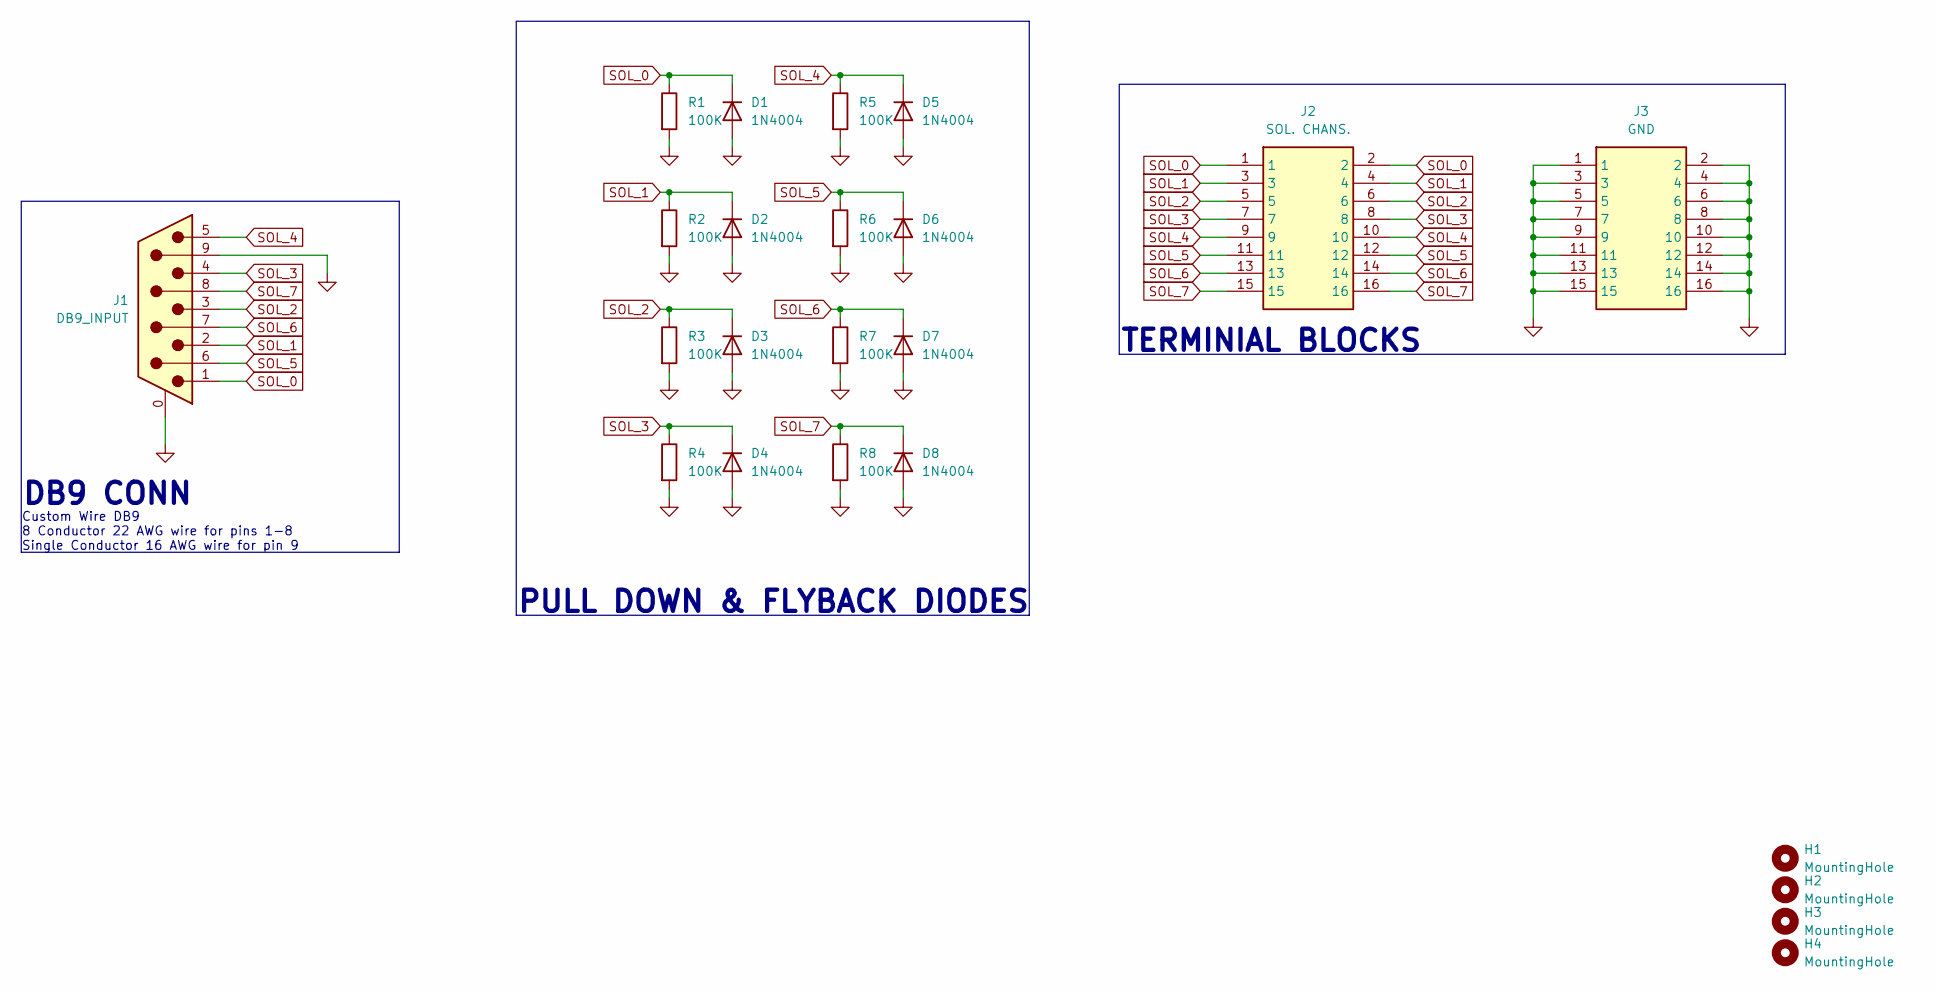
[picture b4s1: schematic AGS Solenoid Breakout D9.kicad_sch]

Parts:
D1, D2, D3, D4, D5, D6, D7, D8: 1N4004; D_DO-41_SOD81_P7.62mm_Horizontal
H1, H2, H3, H4: MountingHole; MountingHole_3.2mm_M3
J1: DB9_INPUT; DSUB-9_Pins_Vertical_P2.77x2.84mm_MountingHoles
J2: SOL. CHANS.; RHDR16W80P550X350_2X8_2870X850X1420P; Mouser Part Number 490-TBLH10V-350-08BK
J3: GND; RHDR16W80P550X350_2X8_2870X850X1420P; Mouser Part Number 490-TBLH10V-350-08BK
R1, R2, R3, R4, R5, R6, R7, R8: 100K; R_Axial_DIN0207_L6.3mm_D2.5mm_P7.62mm_Horizontal

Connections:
GND: D1.2 (A), D2.2 (A), D3.2 (A), D4.2 (A), D5.2 (A), D6.2 (A), D7.2 (A), D8.2 (A), J1.0 (PAD), J1.9, J3.1, J3.2, J3.3, J3.4, J3.5, J3.6, J3.7, J3.8, J3.9, J3.10, J3.11, J3.12, J3.13, J3.14, J3.15, J3.16, R1.2, R2.2, R3.2, R4.2, R5.2, R6.2, R7.2, R8.2
SOL_0: D1.1 (K), J1.1, J2.1, J2.2, R1.1
SOL_1: D2.1 (K), J1.2, J2.3, J2.4, R2.1
SOL_2: D3.1 (K), J1.3, J2.5, J2.6, R3.1
SOL_3: D4.1 (K), J1.4, J2.7, J2.8, R4.1
SOL_4: D5.1 (K), J1.5, J2.9, J2.10, R5.1
SOL_5: D6.1 (K), J1.6, J2.11, J2.12, R6.1
SOL_6: D7.1 (K), J1.7, J2.13, J2.14, R7.1
SOL_7: D8.1 (K), J1.8, J2.15, J2.16, R8.1

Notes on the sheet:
Custom Wire DB9 8 Conductor 22 AWG wire for pins 1-8 Single Conductor 16 AWG wire for pin 9
PULL DOWN & FLYBACK DIODES
TERMINIAL BLOCKS
DB9 CONN

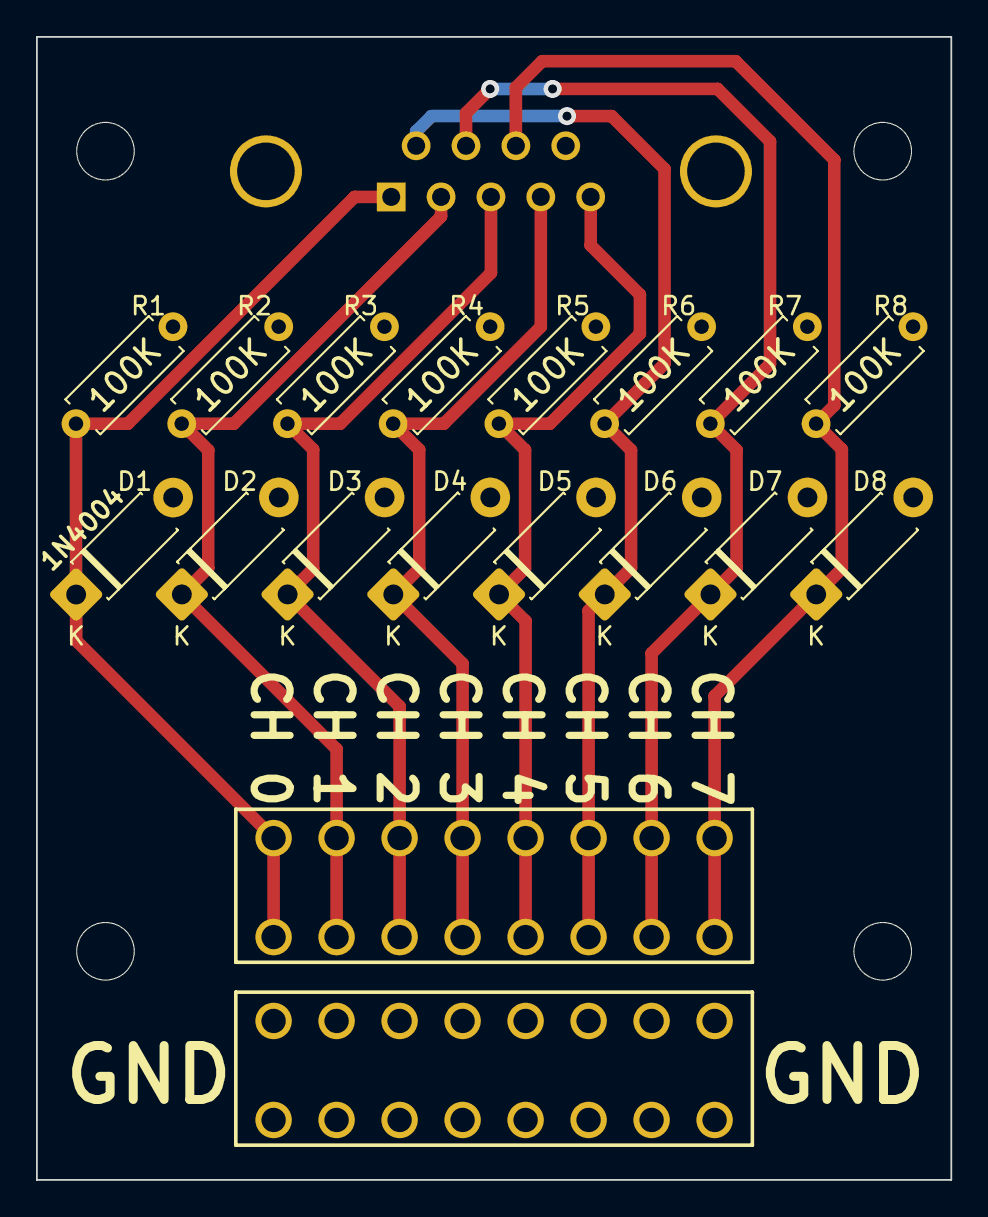
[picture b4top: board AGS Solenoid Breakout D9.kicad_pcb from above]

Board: 2 copper layers, 50.8 x 63.5 mm, 23 parts (1 on the bottom side), 9 nets.

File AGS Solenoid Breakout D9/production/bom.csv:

Designator,Footprint,Quantity,Value,LCSC Part #
"D1, D2, D3, D4, D5, D6, D7, D8",D_DO-41_SOD81_P7.62mm_Horizontal,8,1N4004,
"H1, H2, H3, H4",MountingHole_3.2mm_M3,4,MountingHole,
J1,DSUB-9_Pins_Vertical_P2.77x2.84mm_MountingHoles,1,DB9_INPUT,
"J2, J3",RHDR16W80P550X350_2X8_2870X850X1420P,2,SOL. CHANS.,
"R1, R2, R3, R4, R5, R6, R7, R8",R_Axial_DIN0207_L6.3mm_D2.5mm_P7.62mm_Horizontal,8,100K,

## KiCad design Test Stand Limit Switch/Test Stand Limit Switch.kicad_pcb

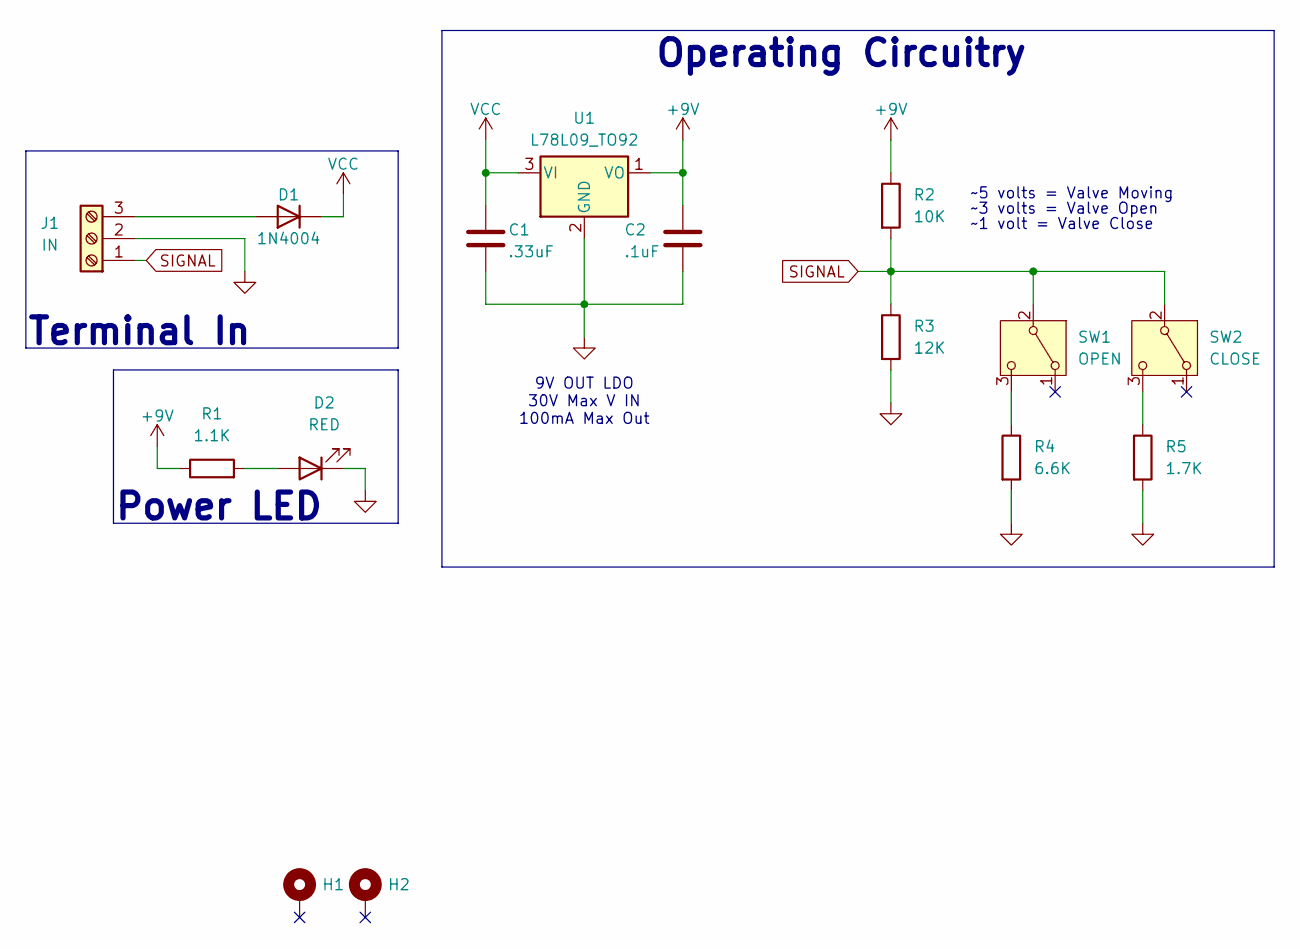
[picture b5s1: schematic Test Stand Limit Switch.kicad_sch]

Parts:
C1: .33uF; C_Disc_D5.0mm_W2.5mm_P2.50mm
C2: .1uF; C_Disc_D5.0mm_W2.5mm_P2.50mm
D1: 1N4004; D_DO-41_SOD81_P7.62mm_Horizontal
D2: RED; LED_D3.0mm
H1, H2: MountingHole_Pad; MountingHole_3.2mm_M3_DIN965_Pad_TopBottom
J1: IN; TerminalBlock_Phoenix_PT-1,5-3-3.5-H_1x03_P3.50mm_Horizontal
R1: 1.1K; R_Axial_DIN0207_L6.3mm_D2.5mm_P7.62mm_Horizontal
R2: 10K; R_Axial_DIN0207_L6.3mm_D2.5mm_P7.62mm_Horizontal
R3: 12K; R_Axial_DIN0207_L6.3mm_D2.5mm_P7.62mm_Horizontal
R4: 6.6K; R_Axial_DIN0207_L6.3mm_D2.5mm_P7.62mm_Horizontal
R5: 1.7K; R_Axial_DIN0207_L6.3mm_D2.5mm_P7.62mm_Horizontal
SW1: OPEN; TerminalBlock_Phoenix_PT-1,5-3-3.5-H_1x03_P3.50mm_Horizontal
SW2: CLOSE; TerminalBlock_Phoenix_PT-1,5-3-3.5-H_1x03_P3.50mm_Horizontal
U1: L78L09_TO92; TO-92L_Inline

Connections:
+9V: C2.1, R1.1, R2.1, U1.1 (VO)
GND: C1.2, C2.2, D2.1 (K), J1.2, R3.2, R4.2, R5.2, U1.2 (GND)
unnamed: D1.2 (A), J1.3
unnamed: D2.2 (A), R1.2
unnamed: R4.1, SW1.3 (C)
unnamed: R5.1, SW2.3 (C)
SIGNAL: J1.1, R2.2, R3.1, SW1.2 (B), SW2.2 (B)
VCC: C1.1, D1.1 (K), U1.3 (VI)

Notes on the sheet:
Operating Circuitry
9V OUT LDO 30V Max V IN 100mA Max Out
Terminal In
~5 volts = Valve Moving
Power LED
~1 volt = Valve Close
~3 volts = Valve Open

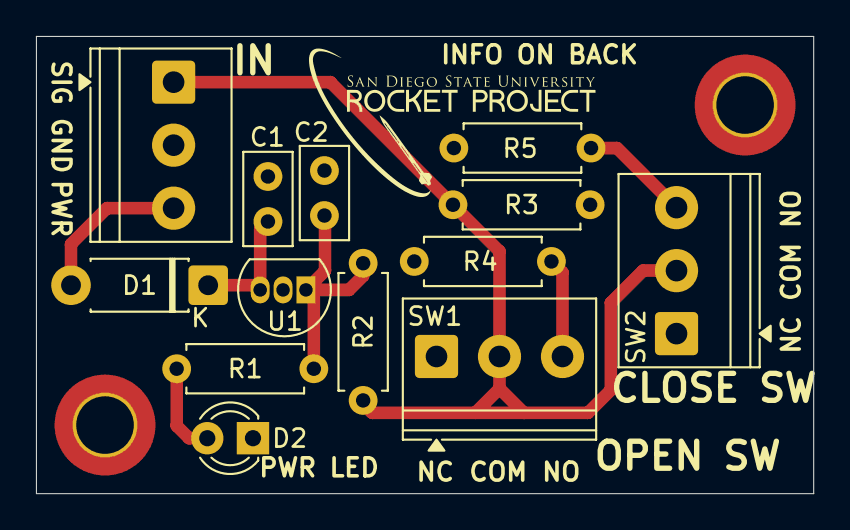
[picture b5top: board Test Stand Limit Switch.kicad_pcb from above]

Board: 2 copper layers, 43.2 x 25.4 mm, 15 parts (0 on the bottom side), 8 nets.

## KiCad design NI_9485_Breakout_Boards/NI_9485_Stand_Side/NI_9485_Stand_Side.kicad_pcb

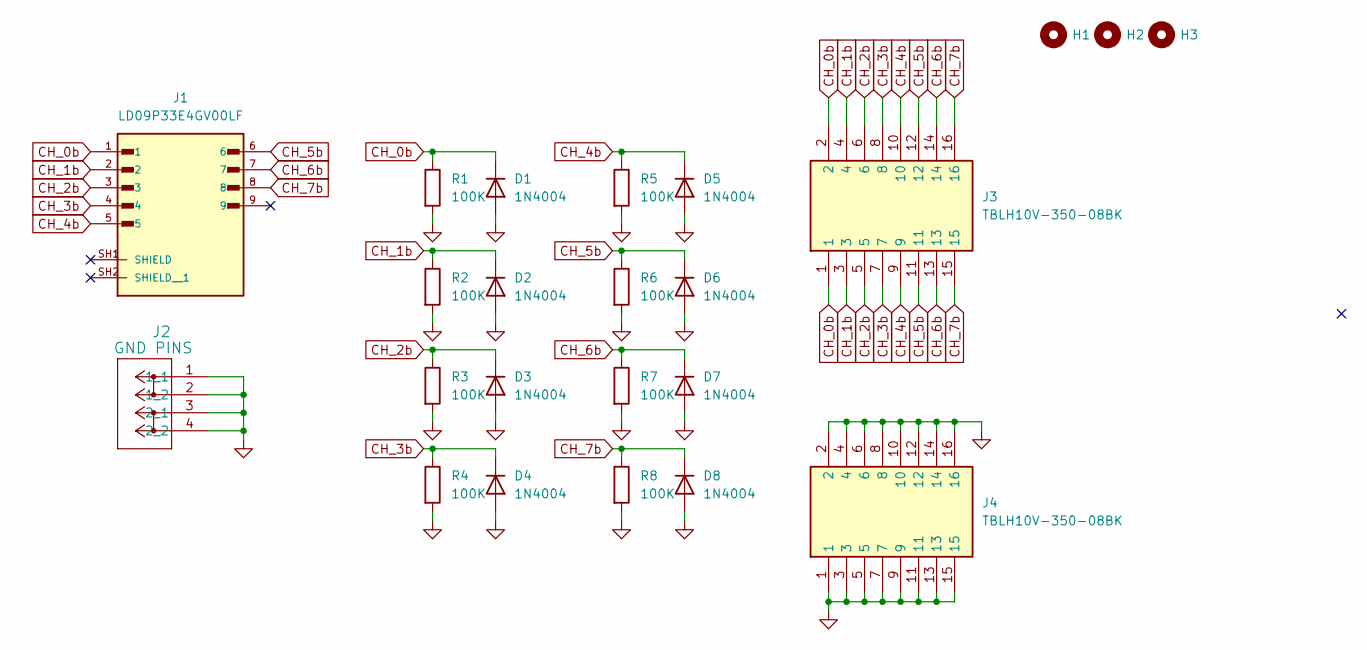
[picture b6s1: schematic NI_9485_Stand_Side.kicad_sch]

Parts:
D1, D2, D3, D4, D5, D6, D7, D8: 1N4004; D_DO-41_SOD81_P7.62mm_Horizontal
H1, H2, H3: MountingHole_Pad; MountingHole_3.2mm_M3_DIN965
J1: LD09P33E4GV00LF; AMPHENOL_LD09P33E4GV00LF; PARTREV B
J2: GND PINS; CONN2_2601-1102_WAG
J3, J4: TBLH10V-350-08BK; RHDR16W80P550X350_2X8_2870X850X1420P; Mouser Part Number 490-TBLH10V-350-08BK
R1, R2, R3, R4, R5, R6, R7, R8: 100K; R_Axial_DIN0207_L6.3mm_D2.5mm_P7.62mm_Horizontal

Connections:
CH_0b: D1.1 (K), J1.1, J3.1, J3.2, R1.1
CH_1b: D2.1 (K), J1.2, J3.3, J3.4, R2.1
CH_2b: D3.1 (K), J1.3, J3.5, J3.6, R3.1
CH_3b: D4.1 (K), J1.4, J3.7, J3.8, R4.1
CH_4b: D5.1 (K), J1.5, J3.9, J3.10, R5.1
CH_5b: D6.1 (K), J1.6, J3.11, J3.12, R6.1
CH_6b: D7.1 (K), J1.7, J3.13, J3.14, R7.1
CH_7b: D8.1 (K), J1.8, J3.15, J3.16, R8.1
GND: D1.2 (A), D2.2 (A), D3.2 (A), D4.2 (A), D5.2 (A), D6.2 (A), D7.2 (A), D8.2 (A), J2.1 (1_1), J2.2 (1_2), J2.3 (2_1), J2.4 (2_2), J4.1, J4.2, J4.3, J4.4, J4.5, J4.6, J4.7, J4.8, J4.9, J4.10, J4.11, J4.12, J4.13, J4.14, J4.15, J4.16, R1.2, R2.2, R3.2, R4.2, R5.2, R6.2, R7.2, R8.2
